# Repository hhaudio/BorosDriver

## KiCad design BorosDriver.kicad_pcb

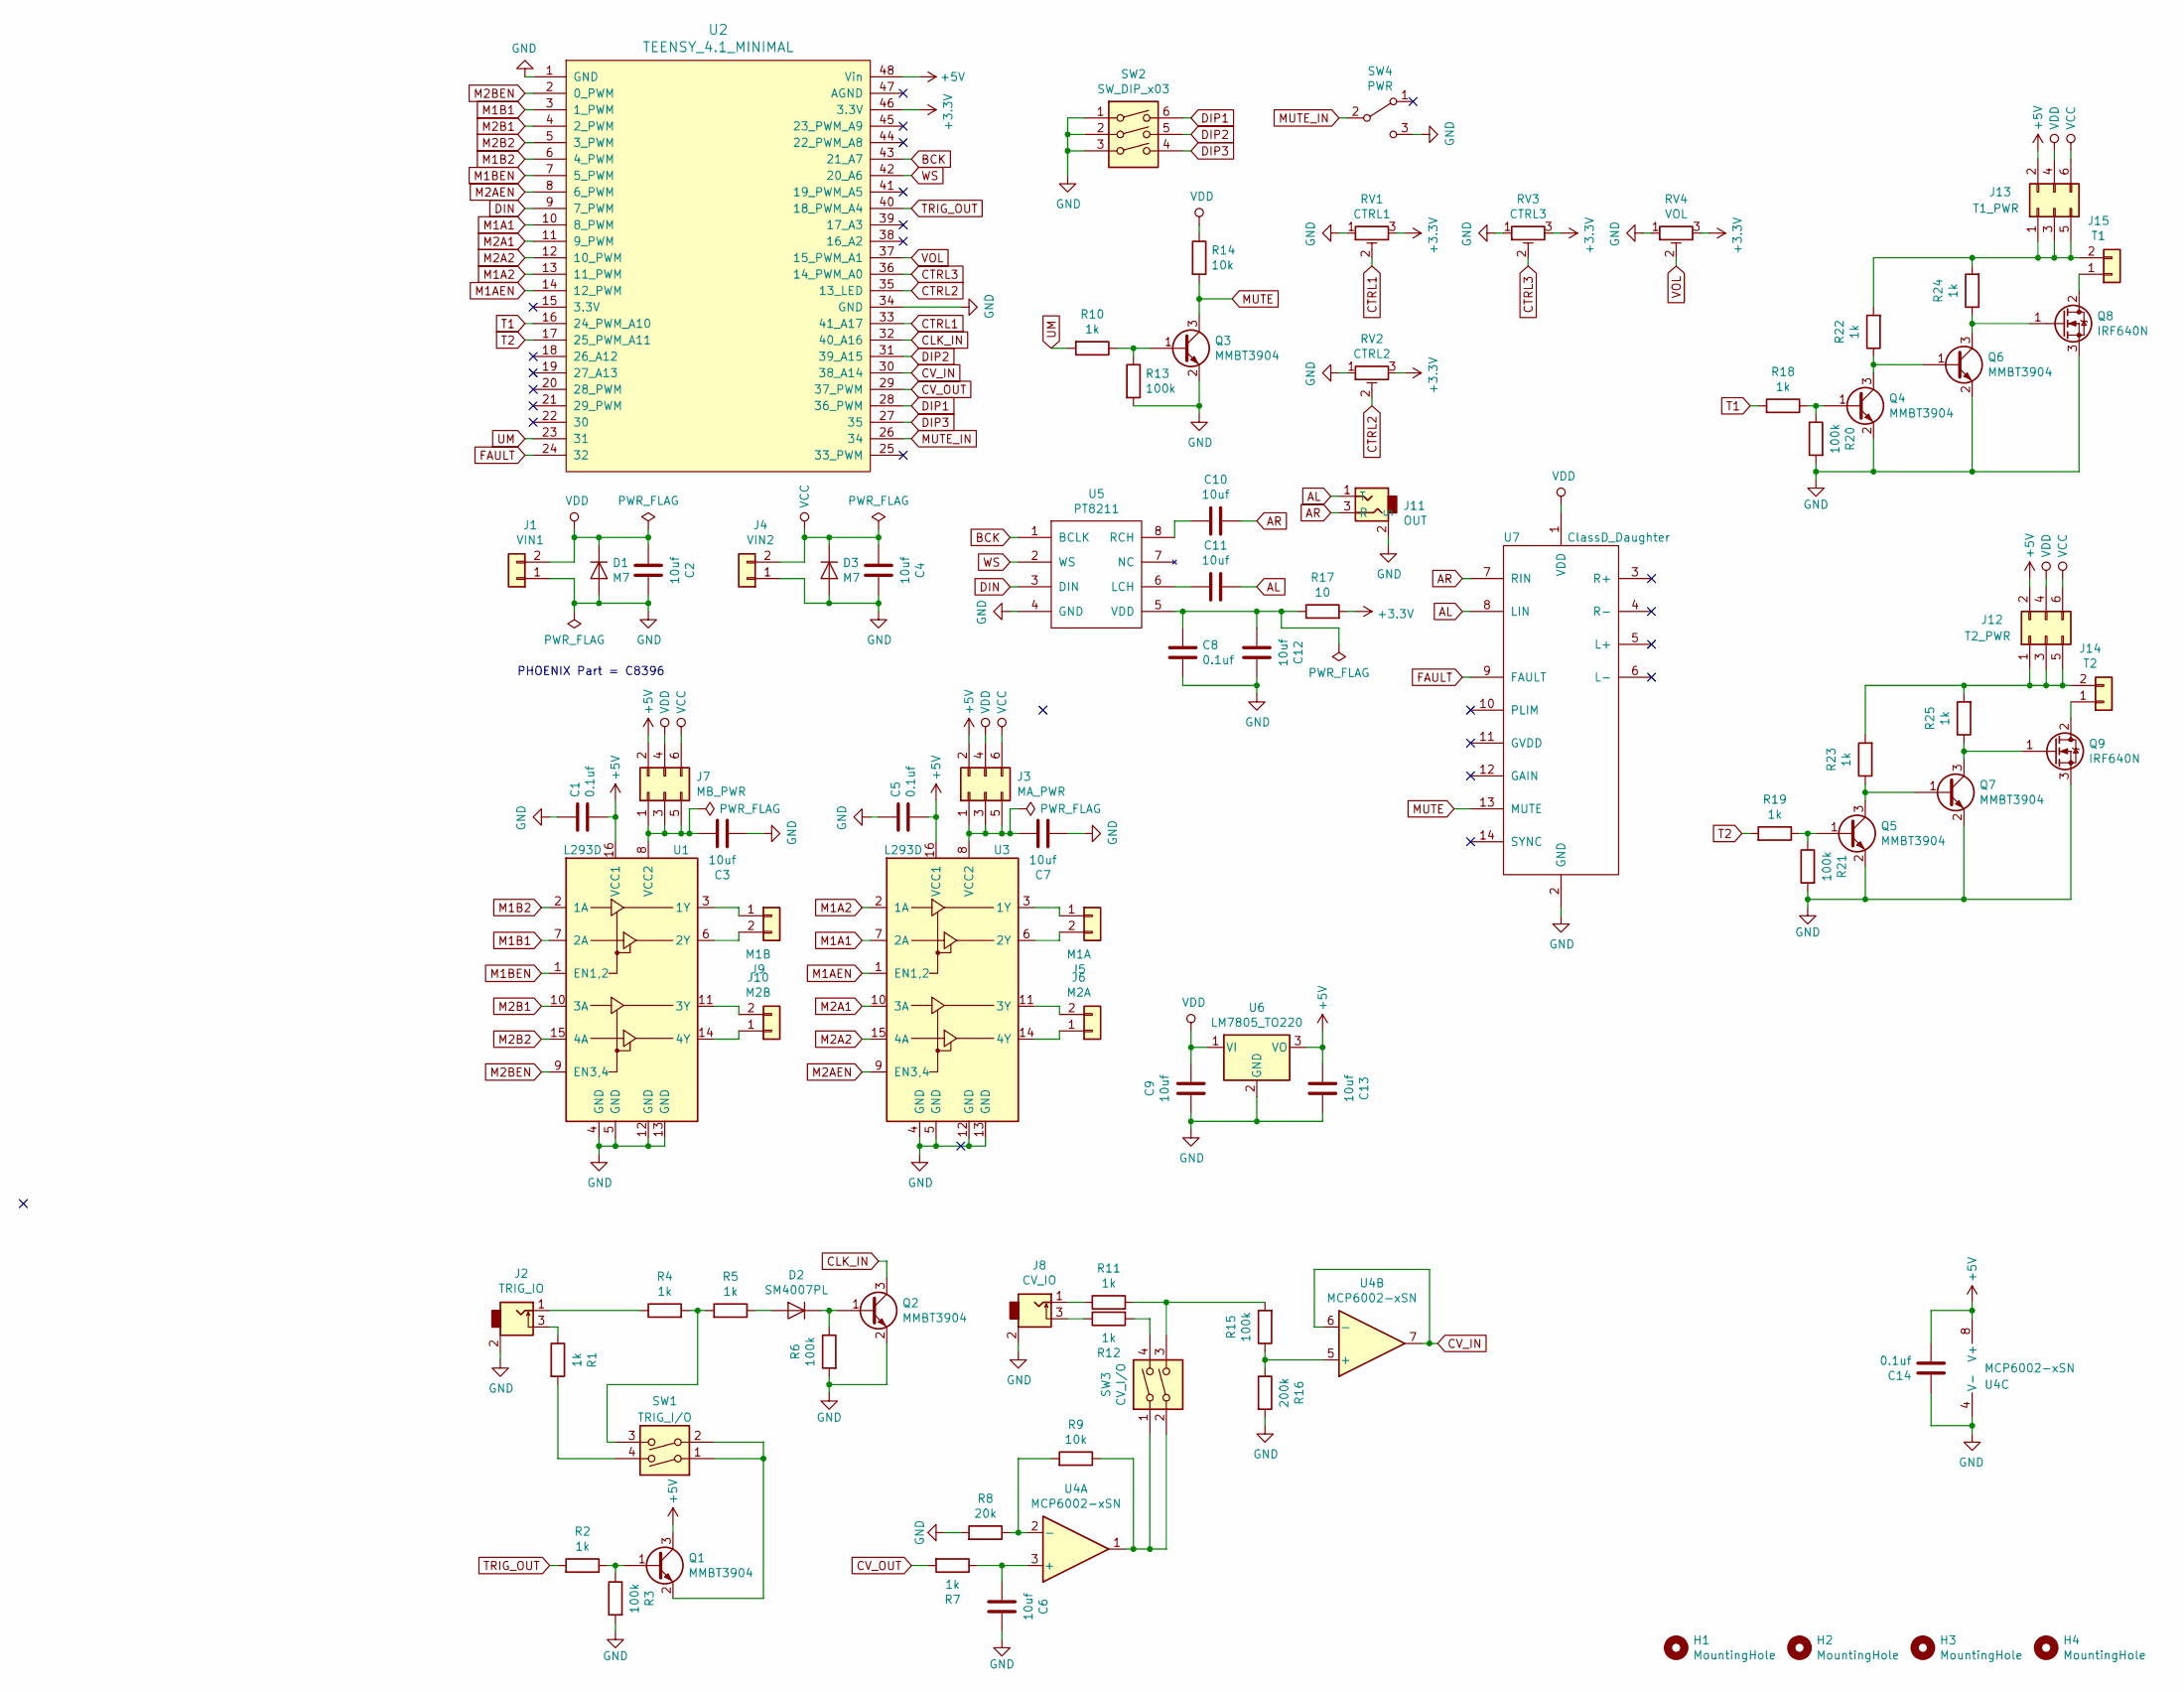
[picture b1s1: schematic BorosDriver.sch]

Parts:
C1, C5, C8, C14: 0.1uf; C_0603_1608Metric_Pad1.05x0.95mm_HandSolder_SmallRef_Top; LCSC C14663
C2, C3, C4, C6, C7, C9, C10, C11, C12, C13: 10uf; C_0603_1608Metric_Pad1.05x0.95mm_HandSolder_SmallRef_Top; LCSC C96446
D1, D3: M7; D_SMA_SmallRef; LCSC C95872
D2: SM4007PL; D_SOD-123; LCSC C64898
H1, H2, H3, H4: MountingHole; M3_MOUNT_KEEPOUT_2
J1: VIN1; Phoenix_Stacked_Marking2_Wider_NoRef_Centered_Val
J2: TRIG_IO; JLC-StereoJack-MonoSwitched-C2764616_VAL; LCSC C2764616
J3: MA_PWR; PinHeader_2x03_P2.54mm_Vertical_SMD_PWR_OPT; LCSC C192301
J4: VIN2; Phoenix_Stacked_Marking2_Wider_NoRef_Centered_Val
J5: M1A; Phoenix_Stacked_Marking2_Wider_NoRef_Centered_Val
J6: M2A; Phoenix_Stacked_Marking2_Wider_NoRef_Centered_Val
J7: MB_PWR; PinHeader_2x03_P2.54mm_Vertical_SMD_PWR_OPT; LCSC C192301
J8: CV_IO; JLC-StereoJack-MonoSwitched-C2764616_VAL; LCSC C2764616
J9: M1B; Phoenix_Stacked_Marking2_Wider_NoRef_Centered_Val
J10: M2B; Phoenix_Stacked_Marking2_Wider_NoRef_Centered_Val
J11: OUT; JLC-StereoJack-TRS-C2764616; LCSC C2764616
J12: T2_PWR; PinHeader_2x03_P2.54mm_Vertical_SMD_PWR_OPT; LCSC C192301
J13: T1_PWR; PinHeader_2x03_P2.54mm_Vertical_SMD_PWR_OPT; LCSC C192301
J14: T2; Phoenix_Stacked_Marking2_Wider_NoRef_Centered_Val
J15: T1; Phoenix_Stacked_Marking2_Wider_NoRef_Centered_Val
Q1, Q2: MMBT3904; SOT-23; LCSC C20526
Q3, Q4, Q5, Q6, Q7: MMBT3904; SOT-23_SmallRef; LCSC C20526
Q8, Q9: IRF640N; TO-220_AssmanSink
R1, R2, R4, R5, R7, R10, R11, R12, R18, R19, R22, R23, R24, R25: 1k; R_0603_1608Metric_Pad1.05x0.95mm_HandSolder_SmallRef_Top; LCSC C21190
R3, R6, R13, R15, R20, R21: 100k; R_0603_1608Metric_Pad1.05x0.95mm_HandSolder_SmallRef_Top; LCSC C25803
R8: 20k; R_0603_1608Metric_Pad1.05x0.95mm_HandSolder_SmallRef_Top; LCSC C4184
R9, R14: 10k; R_0603_1608Metric_Pad1.05x0.95mm_HandSolder_SmallRef_Top; LCSC C25804
R16: 200k; R_0603_1608Metric_Pad1.05x0.95mm_HandSolder_SmallRef_Top; LCSC C25811
R17: 10; R_0603_1608Metric_Pad1.05x0.95mm_HandSolder_SmallRef_Top; LCSC C22859
RV1: CTRL1; SMD_TRIM_JLC_Name; LCSC C128550
RV2: CTRL2; SMD_TRIM_JLC_Name; LCSC C128550
RV3: CTRL3; SMD_TRIM_JLC_Name; LCSC C128550
RV4: VOL; SMD_TRIM_JLC_Name; LCSC C128550
SW1: TRIG_I/O; JLC_SMD_DIP_SPSTx2_C40735; LCSC C40735
SW2: SW_DIP_x03; SMDIP-6_W7.62mm; LCSC C57453
SW3: CV_I/O; JLC_SMD_DIP_SPSTx2_C40735; LCSC C40735
SW4: PWR; JLC_SW_SPDT_SMT_C145845; LCSC C145845
U1, U3: L293D; DIP-16_W7.62mm; LCSC C2326
U2: TEENSY_4.1_MINIMAL; Teensy4.1_SMD_Headers_MidSilk; LCSC C52611
U4: MCP6002-xSN; SOIC-8_3.9x4.9mm_P1.27mm_SmallRef; LCSC C7377
U5: PT8211; SOIC-8_3.9x4.9mm_P1.27mm
U6: LM7805_TO220; TRACO_DCDC
U7: ClassD_Daughter; ClassD_Amp_Mother_Outline_NPTH; LCSC C52711

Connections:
+3V3: R17.2, RV1.3, RV2.3, RV3.3, RV4.3, U2.46 (3.3V)
+5V: C1.2, C5.2, C13.1, C14.2, J3.2, J7.2, J12.2, J13.2, Q1.3 (C), U1.16 (VCC1), U2.48 (Vin), U3.16 (VCC1), U4.8 (V+), U6.3 (VO)
AL: C11.1, J11.1 (T), U7.8 (LIN)
AR: C10.1, J11.3 (R), U7.7 (RIN)
BCK: U2.43 (21_A7), U5.1 (BCLK)
CLK_IN: Q2.3 (C), U2.32 (40_A16)
CTRL1: RV1.2, U2.33 (41_A17)
CTRL2: RV2.2, U2.35 (13_LED)
CTRL3: RV3.2, U2.36 (14_PWM_A0)
CV_IN: U2.30 (38_A14), U4.6 (-), U4.7
CV_OUT: R7.2, U2.29 (37_PWM)
DIN: U2.9 (7_PWM), U5.3 (DIN)
DIP1: SW2.6, U2.28 (36_PWM)
DIP2: SW2.5, U2.31 (39_A15)
DIP3: SW2.4, U2.27 (35)
FAULT: U2.24 (32), U7.9 (FAULT)
GND: C1.1, C2.1, C3.1, C4.1, C5.1, C6.2, C7.1, C8.2, C9.2, C12.2, C13.2, C14.1, D1.2 (A), D3.2 (A), J1.1, J2.2, J4.1, J8.2, J11.2 (S), Q2.2 (E), Q3.2 (E), Q4.2 (E), Q5.2 (E), Q6.2 (E), Q7.2 (E), Q8.3 (S), Q9.3 (S), R3.2, R6.2, R8.2, R13.2, R16.2, R20.2, R21.2, RV1.1, RV2.1, RV3.1, RV4.1, SW2.1, SW2.2, SW2.3, SW4.3 (C), U1.4 (GND), U1.5 (GND), U1.12 (GND), U1.13 (GND), U2.1 (GND), U2.34 (GND), U3.4 (GND), U3.5 (GND), U3.12 (GND), U3.13 (GND), U4.4 (V-), U5.4 (GND), U6.2 (GND), U7.2 (GND)
M1A1: U2.10 (8_PWM), U3.7 (2A)
M1A2: U2.13 (11_PWM), U3.2 (1A)
M1AEN: U2.14 (12_PWM), U3.1 (EN1,2)
M1B1: U1.7 (2A), U2.3 (1_PWM)
M1B2: U1.2 (1A), U2.6 (4_PWM)
M1BEN: U1.1 (EN1,2), U2.7 (5_PWM)
M2A1: U2.11 (9_PWM), U3.10 (3A)
M2A2: U2.12 (10_PWM), U3.15 (4A)
M2AEN: U2.8 (6_PWM), U3.9 (EN3,4)
M2B1: U1.10 (3A), U2.4 (2_PWM)
M2B2: U1.15 (4A), U2.5 (3_PWM)
M2BEN: U1.9 (EN3,4), U2.2 (0_PWM)
MUTE: Q3.3 (C), R14.2, U7.13 (MUTE)
MUTE_IN: SW4.2 (B), U2.26 (34)
unnamed: C3.2, J7.1, J7.3, J7.5, U1.8 (VCC2)
unnamed: C6.1, R7.1, U4.3 (+)
unnamed: C7.2, J3.1, J3.3, J3.5, U3.8 (VCC2)
unnamed: C10.2, U5.8 (RCH)
unnamed: C11.2, U5.6 (LCH)
unnamed: C8.1, C12.1, R17.1, U5.5 (VDD)
unnamed: D2.1 (K), Q2.1 (B), R6.1
unnamed: D2.2 (A), R5.1
unnamed: J2.1, R4.1
unnamed: J2.3, R1.1
unnamed: J5.1, U3.3 (1Y)
unnamed: J5.2, U3.6 (2Y)
unnamed: J6.1, U3.14 (4Y)
unnamed: J6.2, U3.11 (3Y)
unnamed: J8.1, R11.1
unnamed: J8.3, R12.1
unnamed: J9.1, U1.3 (1Y)
unnamed: J9.2, U1.6 (2Y)
unnamed: J10.1, U1.14 (4Y)
unnamed: J10.2, U1.11 (3Y)
unnamed: J12.1, J12.3, J12.5, J14.2, R23.2, R25.2
unnamed: J13.1, J13.3, J13.5, J15.2, R22.2, R24.2
unnamed: J14.1, Q9.2 (D)
unnamed: J15.1, Q8.2 (D)
unnamed: Q1.1 (B), R2.1, R3.1
unnamed: Q1.2 (E), SW1.1, SW1.2
unnamed: Q3.1 (B), R10.1, R13.1
unnamed: Q4.1 (B), R18.1, R20.1
unnamed: Q4.3 (C), Q6.1 (B), R22.1
unnamed: Q5.1 (B), R19.1, R21.1
unnamed: Q5.3 (C), Q7.1 (B), R23.1
unnamed: Q6.3 (C), Q8.1 (G), R24.1
unnamed: Q7.3 (C), Q9.1 (G), R25.1
unnamed: R1.2, SW1.4
unnamed: R4.2, R5.2, SW1.3
unnamed: R8.1, R9.2, U4.2 (-)
unnamed: R9.1, SW3.1, SW3.2, U4.1
unnamed: R11.2, R15.2, SW3.3
unnamed: R12.2, SW3.4
unnamed: R15.1, R16.1, U4.5 (+)
T1: R18.2, U2.16 (24_PWM_A10)
T2: R19.2, U2.17 (25_PWM_A11)
TRIG_OUT: R2.2, U2.40 (18_PWM_A4)
UM: R10.2, U2.23 (31)
VCC: C4.2, D3.1 (K), J3.6, J4.2, J7.6, J12.6, J13.6
VDD: C2.2, C9.1, D1.1 (K), J1.2, J3.4, J7.4, J12.4, J13.4, R14.1, U6.1 (VI), U7.1 (VDD)
VOL: RV4.2, U2.37 (15_PWM_A1)
WS: U2.42 (20_A6), U5.2 (WS)

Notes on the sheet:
PHOENIX Part = C8396

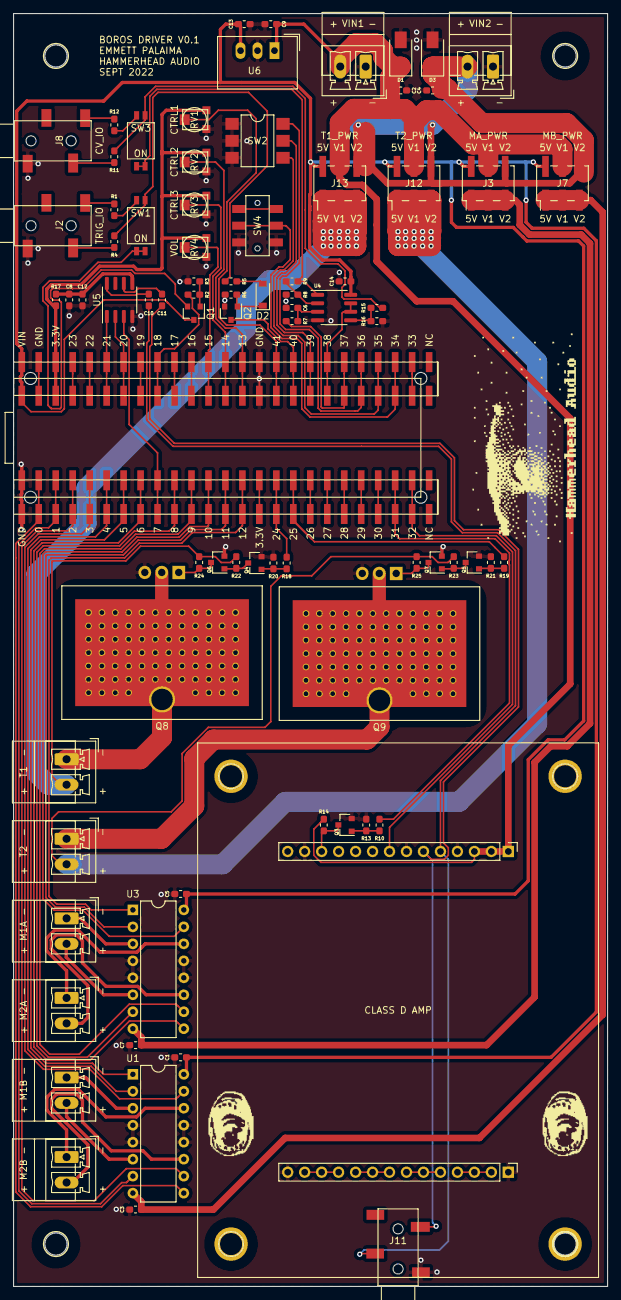
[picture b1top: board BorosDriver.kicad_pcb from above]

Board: 2 copper layers, 88.9 x 190.5 mm, 86 parts (0 on the bottom side), 79 nets.

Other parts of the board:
HH_LOGO_32x16: HH_LOGO_32x16

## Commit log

2022-09-04 components placed
2022-09-04 layout progress
2022-09-05 layout finished
